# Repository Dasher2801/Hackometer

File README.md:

# Stardance CO2 & Environmental Monitor

A custom-designed, compact environmental monitoring board powered by the **ESP32-C3** microcontroller. This project features a high-precision **Sensirion SCD40** sensor to track CO2 levels, temperature, and relative humidity. Designed as part of the Hack Club Stardance hardware challenge.

---

## 🚀 Features

* **Brainpower:** Powered by the RISC-V ESP32-C3-WROOM-02 module supporting Wi-Fi and Bluetooth LE.
* **Precision Sensing:** Integrated Sensirion SCD40 for true photoacoustic $CO_2$ readings, ambient temperature, and humidity.
* **Thermal Isolation:** Features a dedicated physical PCB milling slot (isolation rout) to separate the sensor from the ESP32's operational heat, ensuring highly accurate temperature readings.
* **Display Output:** Dedicated I2C header pins to plug in a standard 0.96" SSD1306 OLED display.
* **Modern Interface:** USB-C connection for reliable power supply and easy flashing/debugging.
* **Hand-Solder Friendly:** Passive components use the 0805 SMD footprint, making it perfectly optimized for easy manual assembly.

---

## 🛠️ Hardware Architecture

### Key Components
* **MCU:** ESP32-C3-WROOM-02
* **Sensor:** Sensirion SCD40-D-R2 (LGA-20)
* **Power Regulator:** AP2112K-3.3V LDO (SOT-23-5)
* **Connector:** 16-pin USB-C (HRO TYPE-C-31-M-12)

### Pin Mapping
* **I2C SDA:** GPIO 8
* **I2C SCL:** GPIO 9
* **USB D-:** GPIO 18
* **USB D+:** GPIO 19

---

## 📁 Repository Structure

* `/hardware` - Contains the KiCad project files, schematics, and PCB layouts.
* `/gerbers` - Production-ready Gerber and Drill files (`.zip` format) for manufacturing.
* `BOM.md` - Complete Bill of Materials with exact hardware designators and component values.

---

## 🔧 Production & Assembly Notes

1. **PCB Fabrication:** The Gerber files are optimized for standard 2-layer manufacturing (1.6mm thickness recommended). Ensure your manufacturer supports internal cutouts/slots for the thermal isolation barrier.
2. **RF Performance:** The top edge of the PCB keeps a strict copper-free clearance zone around the ESP32 onboard antenna to guarantee optimal Wi-Fi and Bluetooth signal strength.
3. **Soldering the SCD40:** Because the SCD40 is an LGA package with pads located entirely underneath the chip, utilizing solder paste and a hot-air rework station (or a reflow heat plate) is highly recommended for assembly.

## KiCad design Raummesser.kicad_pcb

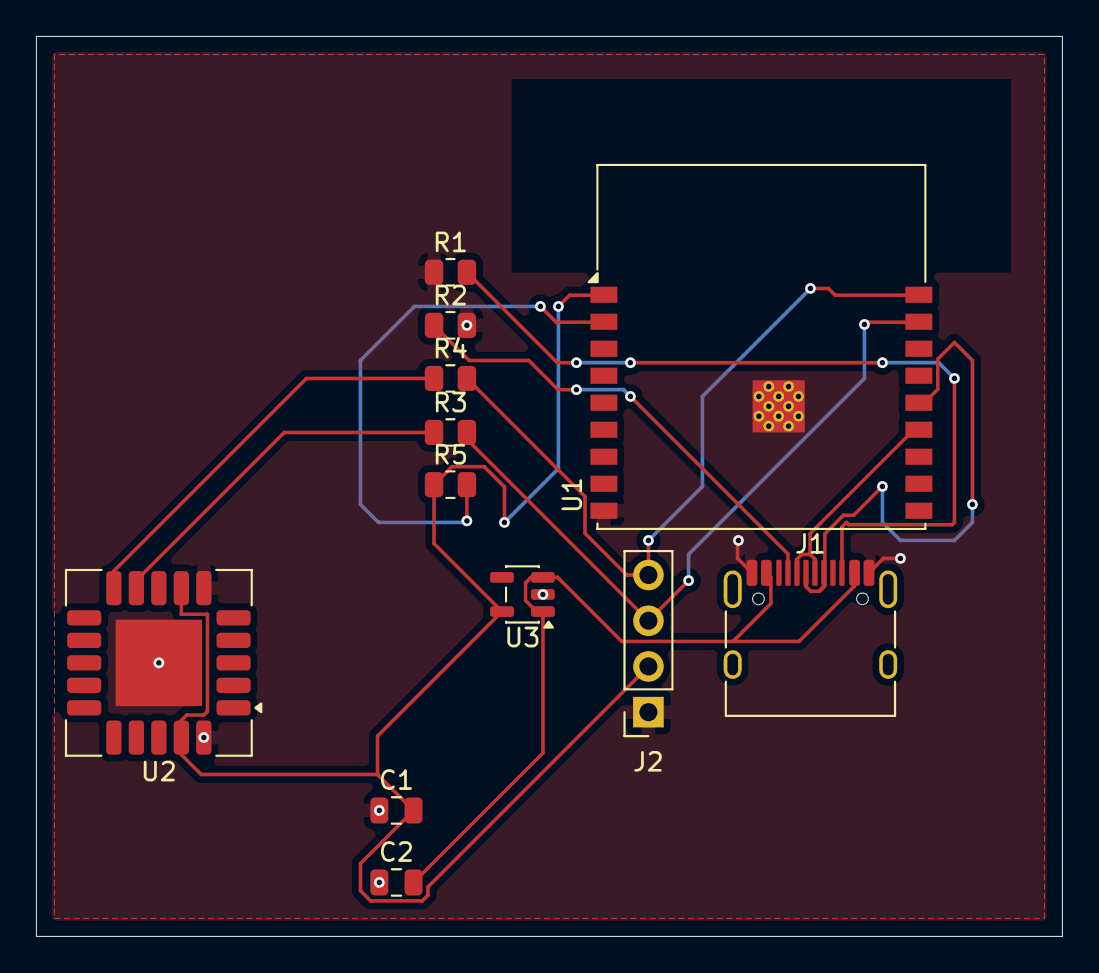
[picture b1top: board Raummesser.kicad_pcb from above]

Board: 2 copper layers, 57.0 x 50.0 mm, 12 parts (0 on the bottom side), 11 nets.

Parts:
C1, C2: 10µF; C_0805_2012Metric
J1: USB_C_Receptacle_USB2.0_16P; USB_C_Receptacle_HRO_TYPE-C-31-M-12
J2: Display; PinSocket_1x04_P2.54mm_Vertical
R1: 5.1k; R_0805_2012Metric
R2: 5,1k; R_0805_2012Metric
R3, R4: 4,7k; R_0805_2012Metric
R5: 10k; R_0805_2012Metric
U1: ESP32-C3-WROOM-02
U2: SCD40-D-R2; Sensirion_SCD4x-1EP_10.1x10.1mm_P1.25mm_EP4.8x4.8mm
U3: AP2112K-3.3; SOT-23-5

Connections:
GND: C1.1, C2.1, J1.A1 (GND), J1.A12 (GND), J1.B1 (GND), J1.B12 (GND), J2.1, R1.1, R2.2, U1.9 (GND), U1.19 (GND), U2.6 (GND), U2.20 (GND), U2.21 (GND), U3.2 (GND)
unnamed: J1.A5 (CC1), J1.A6 (D+), J1.B6 (D+), R2.1, U1.14 (IO19)
unnamed: J1.B5 (CC2), R1.2
unnamed: C1.2, J2.2, R5.1, U1.1 (3V3), U2.7 (VDD), U2.19 (VDD), U3.5 (VOUT)
unnamed: J2.3, R3.2, U1.17 (IO1)
unnamed: J2.4, R4.2, U1.18 (IO0)
unnamed: R5.2, U1.2 (EN)
unnamed: J1.A7 (D-), J1.B7 (D-), U1.13 (IO18)
unnamed: R3.1, U2.9 (SCL)
unnamed: R4.1, U2.10 (SDA)
unnamed: C2.2, J1.A4 (VBUS), J1.A9 (VBUS), J1.B4 (VBUS), J1.B9 (VBUS), U3.1 (VIN), U3.3 (EN)
